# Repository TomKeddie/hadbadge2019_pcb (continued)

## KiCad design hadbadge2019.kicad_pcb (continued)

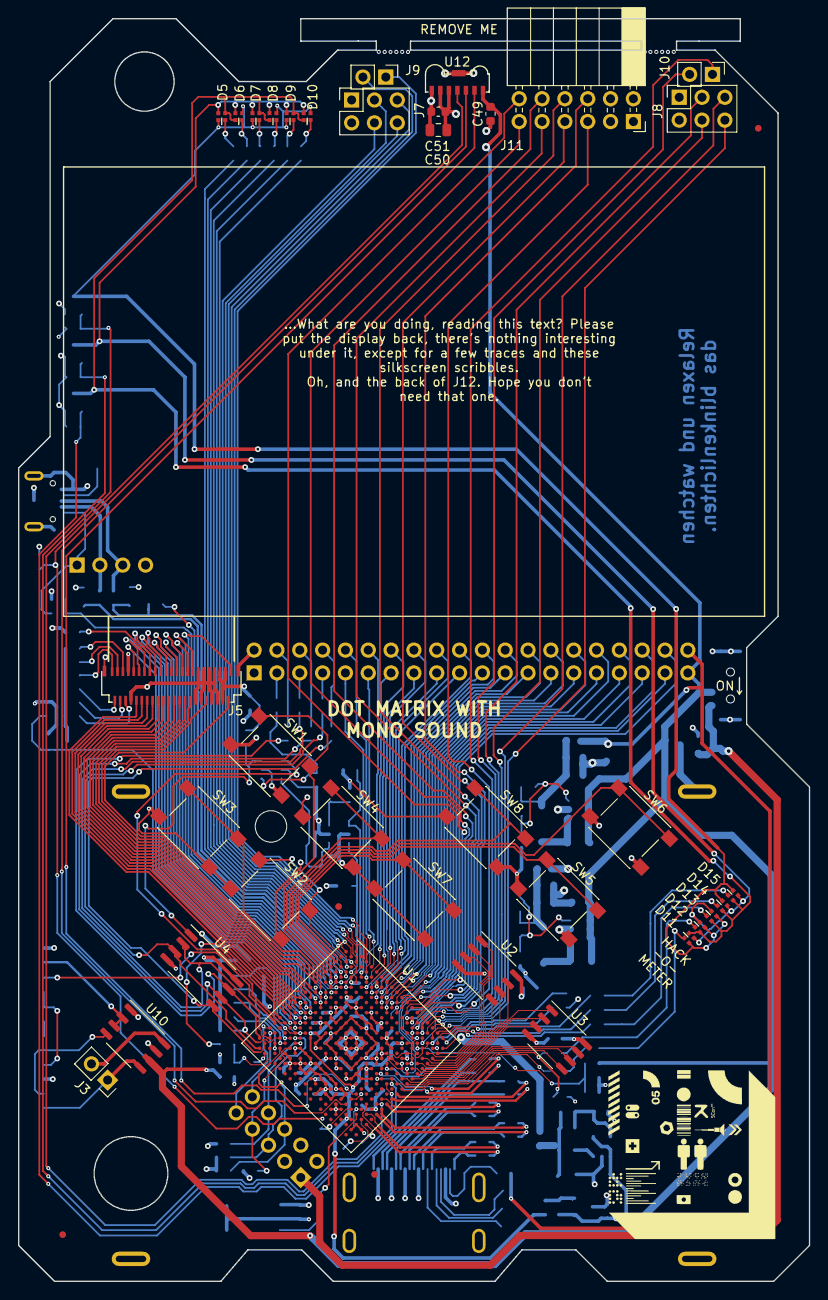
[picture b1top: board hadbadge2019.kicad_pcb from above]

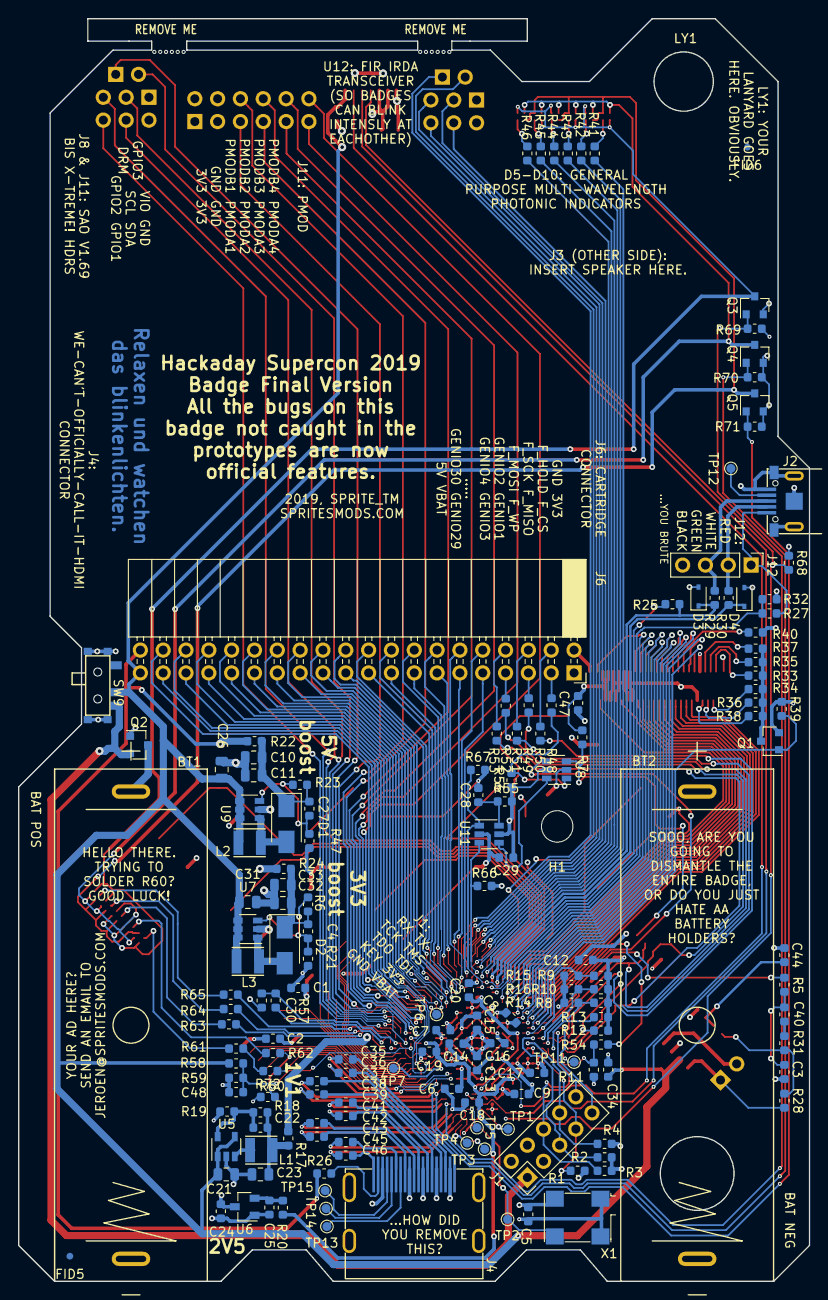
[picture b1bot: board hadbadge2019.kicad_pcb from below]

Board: 4 copper layers, 88.0 x 140.5 mm, 202 parts (162 on the bottom side), 235 nets.

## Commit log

2019-11-07 Added measurements Labelled jtag signals
